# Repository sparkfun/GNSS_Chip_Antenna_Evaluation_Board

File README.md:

SparkFun GNSS Chip Antenna Evaluation Board
===========================================================

[*SparkFun GNSS Chip Antenna Eval Board (GPS-15247)*](https://www.sparkfun.com/products/15247)

The GNSS Chip Evaluation board allows for quick testing of various chip scale GPS and GNSS antennas. Various sizes and manufacturers allow the user to see for themselves how their GPS receiver will preform with each extremely small GPS antenna.

Repository Contents
-------------------

* **/Documents** - Antenna datasheets
* **/Hardware** - Eagle files

Documentation
-------------------

* **[Hookup Guide](https://learn.sparkfun.com/tutorials/gnss-chip-antenna-hookup-guide)** - Basic hookup guide for the antenna evaluation board
* **[Three Quick Tips About Using U.FL](https://learn.sparkfun.com/tutorials/three-quick-tips-about-using-ufl)** - Quick tips regarding how to connect, protect, and disconnect U.FL connectors

License Information
-------------------

This product is _**open source**_! 

Various bits of the code have different licenses applied. Anything SparkFun wrote is beerware; if you see me (or any other SparkFun employee) at the local, and you've found our code helpful, please buy us a round!

Please use, reuse, and modify these files as you see fit. Please maintain attribution to SparkFun Electronics and release anything derivative under the same license.

Distributed as-is; no warranty is given.

- Your friends at SparkFun.

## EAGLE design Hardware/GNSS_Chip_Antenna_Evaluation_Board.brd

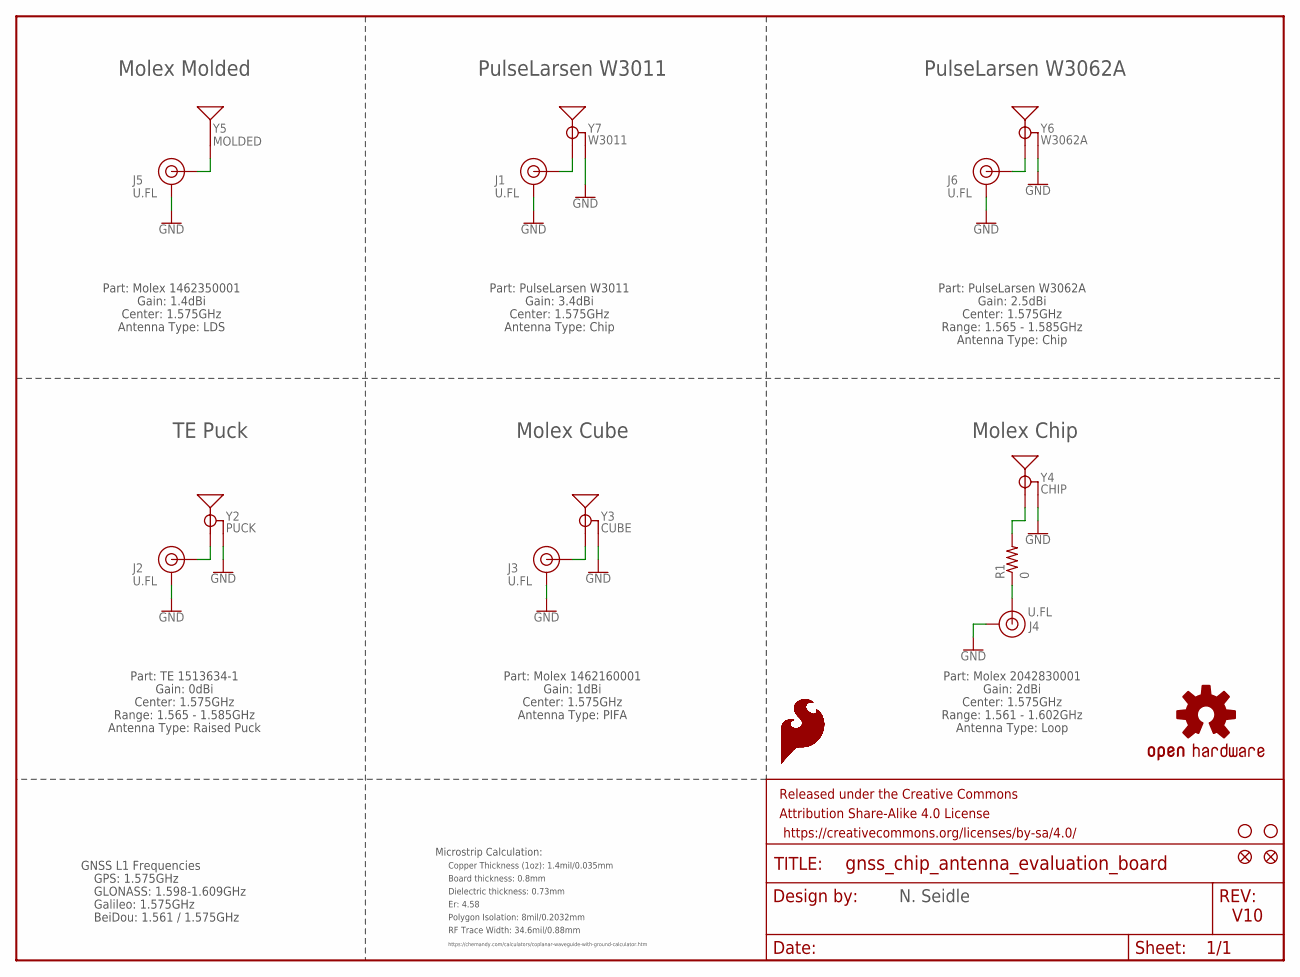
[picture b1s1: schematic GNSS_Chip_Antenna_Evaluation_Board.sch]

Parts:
FRAME1: FRAME-LETTER; CREATIVE_COMMONS
J1, J2, J3, J4, J5, J6: U.FL
JP5, JP6: STAND-OFF
JP8, JP9: FIDUCIAL1X2; FIDUCIAL-1X2
LOGO1, LOGO2, LOGO3, LOGO4, LOGO5, LOGO6: SFE_LOGO_FLAME.1EXP; SFE_LOGO_FLAME_COPPER_EXPOSED_.1
R1: 0; 0402
U$16: OSHW-LOGOS; OSHW-LOGO-S
Y2: PUCK; TE_PUCK
Y3: CUBE; MOLEX_GNSS_CUBE
Y4: CHIP; MOLEX_GNSS_CHIP
Y5: MOLDED; MLOEX_GNSS_MOLDED
Y6: W3062A
Y7: W3011

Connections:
FEED1: J1.FEED (SIGNAL), Y7.1 (SIGNAL)
FEED2: J5.FEED (SIGNAL), Y5.FEED
FEED3: J2.FEED (SIGNAL), Y2.S (SIGNAL)
FEED4: J3.FEED (SIGNAL), Y3.FEED (SIGNAL)
FEED5: J4.FEED (SIGNAL), R1.1
FEED6: J6.FEED (SIGNAL), Y6.FEED (SIGNAL)
GND: J1.1 (GND), J1.2 (GND), J2.1 (GND), J2.2 (GND), J3.1 (GND), J3.2 (GND), J4.1 (GND), J4.2 (GND), J5.1 (GND), J5.2 (GND), J6.1 (GND), J6.2 (GND), Y2.1 (GND), Y2.2 (GND), Y2.3 (GND), Y3.GND, Y4.1 (GND), Y4.2 (GND), Y4.3 (GND), Y6.GND, Y7.2 (GND), Y7.3 (GND)
unnamed: R1.2, Y4.FEED (SIGNAL)

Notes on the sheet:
V10
Board thickness: 0.8mm
Er: 4.58
Copper Thickness (1oz): 1.4mil/0.035mm
RF Trace Width: 34.6mil/0.88mm
Polygon Isolation: 8mil/0.2032mm
Dielectric thickness: 0.73mm
https://chemandy.com/calculators/coplanar-waveguide-with-ground-calculator.htm
Microstrip Calculation:
Center: 1.575GHz
Gain: 1.4dBi
Part: Molex 1462350001
Range: 1.565 - 1.585GHz
Gain: 2.5dBi
Part: PulseLarsen W3062A
Gain: 3.4dBi
Part: PulseLarsen W3011
Gain: 1dBi
Part: Molex 1462160001
Gain: 0dBi
Part: TE 1513634-1
Range: 1.561 - 1.602GHz
Gain: 2dBi
Part: Molex 2042830001
Antenna Type: Chip
Antenna Type: Loop
Antenna Type: PIFA
Antenna Type: Raised Puck
Antenna Type: LDS
GPS: 1.575GHz
GLONASS: 1.598-1.609GHz
Galileo: 1.575GHz
BeiDou: 1.561 / 1.575GHz
Molex Molded
Molex Chip
Molex Cube
PulseLarsen W3062A
PulseLarsen W3011
TE Puck
N. Seidle

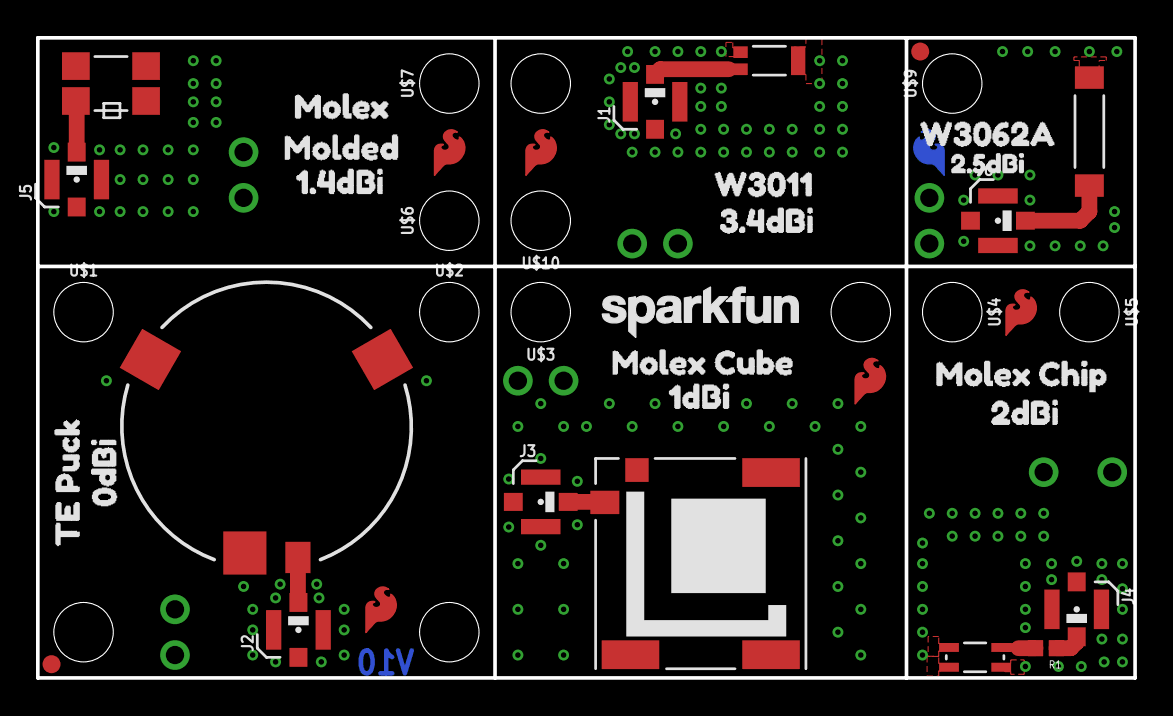
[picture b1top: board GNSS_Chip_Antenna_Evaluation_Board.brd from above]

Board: 2 copper layers, 61.0 x 35.6 mm, 74 parts (25 on the bottom side), 8 nets.

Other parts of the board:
JP1, JP2: STAND-OFF
U$1, U$2, U$3, U$4, U$5, U$6, U$7, U$9, U$10: STAND-OFF
U$8, U$24, U$25, U$26, U$27, U$28: ANCHOR0
U$11, U$34: 3#4DBI2
U$12, U$42: 0DBI0
U$13, U$57: TE_PUCK7
U$14, U$32: 1#4DBI3
U$15, U$39: 1DBI1
U$17: ORDERING_INSTRUCTIONS
U$18, U$38: 2DBI2
U$19, U$20: MOLEX_CHIP5
U$21, U$22: MOLEX0
U$23: SFE_LOGO_NAME_.1
U$29, U$30: MOLDED1
U$31, U$56: MOLEX_CUBE6
U$33, U$59: W30112
U$35, U$58: W3062A3
U$36: 2#5DBI4
U$37: SFE_LOGO_NAME_FLAME_.1
U$43: ANTENNA10
U$44: 2#5DBI2
U$50: EVALUATION_BOARD15
U$52: GNSS_CHIP13

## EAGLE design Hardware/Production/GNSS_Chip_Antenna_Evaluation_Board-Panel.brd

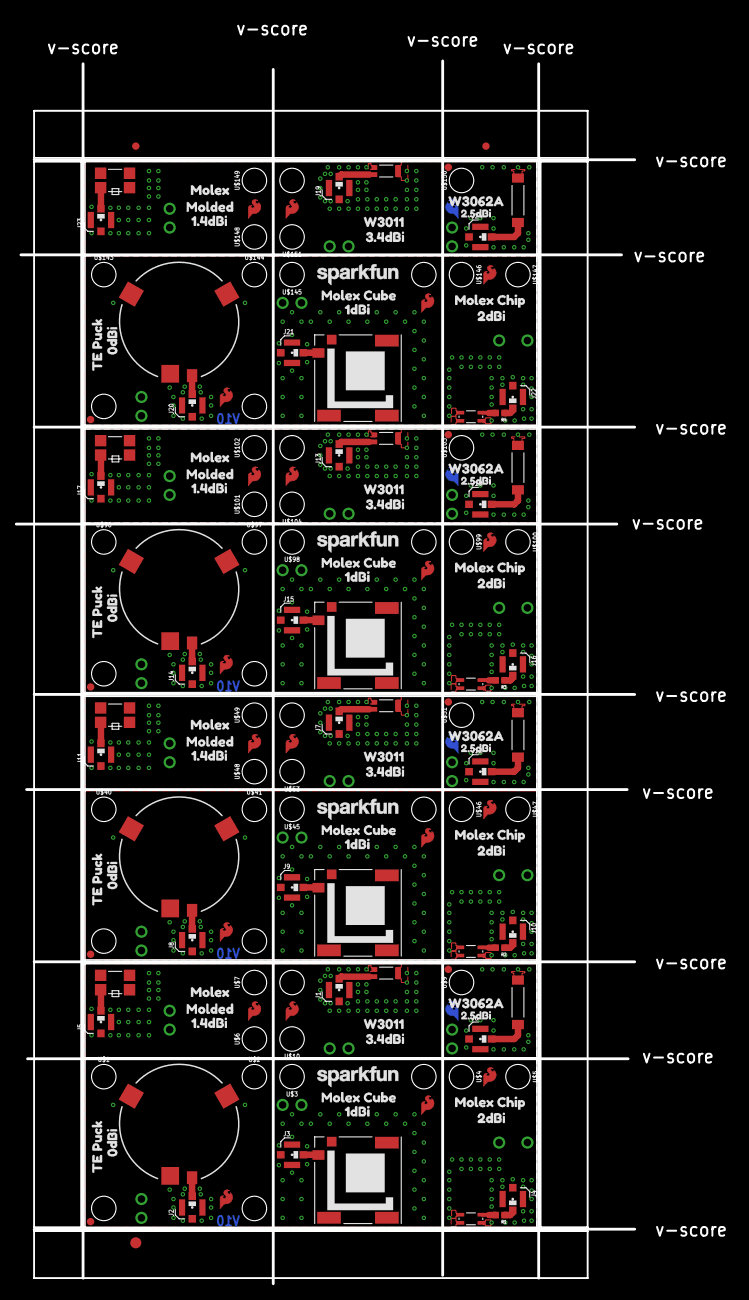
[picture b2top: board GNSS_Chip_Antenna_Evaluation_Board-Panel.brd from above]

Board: 2 copper layers, 96.6 x 171.0 mm, 291 parts (100 on the bottom side), 32 nets.

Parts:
E$1, E$2: FIDUCIAL-1X2
E$3: FIDUCIAL-1.5X3
J1, J2, J3, J4, J5, J6, J7, J8, J9, J10, J11, J12, J13, J14, J15, J16, J17, J18, J19, J20, J21, J22, J23, J24: U.FL
JP1, JP2, JP3, JP4, JP5, JP6, JP11, JP12, JP13, JP14, JP17, JP18, JP19, JP20, JP23, JP24: STAND-OFF
JP7, JP8, JP9, JP10, JP15, JP16, JP21, JP22: FIDUCIAL1X2; FIDUCIAL-1X2
LOGO1, LOGO2, LOGO3, LOGO4, LOGO5, LOGO6, LOGO7, LOGO8, LOGO9, LOGO10, LOGO11, LOGO12, LOGO13, LOGO14, LOGO15, LOGO16, LOGO17, LOGO18, LOGO19, LOGO20, LOGO21, LOGO22, LOGO23, LOGO24: SFE_LOGO_FLAME.1EXP; SFE_LOGO_FLAME_COPPER_EXPOSED_.1
R1, R2, R3, R4: 0; 0402
U$1, U$2, U$3, U$4, U$5, U$6, U$7, U$9, U$10, U$40, U$41, U$45, U$46, U$47, U$48, U$49, U$51, U$53, U$96, U$97, U$98, U$99, U$100, U$101, U$102, U$103, U$104, U$143, U$144, U$145, U$146, U$147, U$148, U$149, U$150, U$151: STAND-OFF
U$8, U$24, U$25, U$26, U$27, U$28, U$63, U$64, U$65, U$66, U$67, U$68, U$110, U$111, U$112, U$113, U$114, U$115, U$157, U$158, U$159, U$160, U$161, U$162: ANCHOR0
U$11, U$34, U$54, U$70, U$105, U$117, U$152, U$164: 3#4DBI2
U$12, U$42, U$55, U$74, U$106, U$121, U$153, U$168: 0DBI0
U$13, U$57, U$81, U$84, U$128, U$131, U$175, U$178: TE_PUCK7
U$14, U$32, U$60, U$69, U$107, U$116, U$154, U$163: 1#4DBI3
U$15, U$39, U$61, U$73, U$108, U$120, U$155, U$167: 1DBI1
U$16, U$17, U$95, U$142: OSHW-LOGOS; OSHW-LOGO-S
U$18, U$38, U$62, U$72, U$109, U$119, U$156, U$166: 2DBI2
U$19, U$20, U$85, U$86, U$132, U$133, U$179, U$180: MOLEX_CHIP5
U$21, U$22, U$87, U$89, U$134, U$136, U$181, U$183: MOLEX0
U$23, U$76, U$123, U$170: SFE_LOGO_NAME_.1
U$29, U$30, U$88, U$90, U$135, U$137, U$182, U$184: MOLDED1
U$31, U$56, U$80, U$91, U$127, U$138, U$174, U$185: MOLEX_CUBE6
U$33, U$59, U$83, U$92, U$130, U$139, U$177, U$186: W30112
U$35, U$58, U$82, U$93, U$129, U$140, U$176, U$187: W3062A3
U$36, U$71, U$118, U$165: 2#5DBI4
U$37, U$94, U$141, U$188: SFE_LOGO_NAME_FLAME_.1
U$43, U$77, U$124, U$171: ANTENNA10
U$44, U$75, U$122, U$169: 2#5DBI2
U$50, U$78, U$125, U$172: EVALUATION_BOARD15
U$52, U$79, U$126, U$173: GNSS_CHIP13
Y1, Y2, Y13, Y19: PUCK; TE_PUCK
Y3, Y8, Y14, Y20: CUBE; MOLEX_GNSS_CUBE
Y4, Y9, Y15, Y21: CHIP; MOLEX_GNSS_CHIP
Y5, Y10, Y16, Y22: MOLDED; MLOEX_GNSS_MOLDED
Y6, Y11, Y17, Y23: W3062A
Y7, Y12, Y18, Y24: W3011

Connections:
FEED1: J1.FEED, Y7.1
FEED2: J5.FEED, Y5.FEED
FEED3: J2.FEED, Y2.S
FEED4: J3.FEED, Y3.FEED
FEED5: J4.FEED, R1.1
FEED6: J6.FEED, Y6.FEED
FEED7: J7.FEED, Y12.1
FEED8: J8.FEED, Y1.S
FEED9: J9.FEED, Y8.FEED
FEED10: J10.FEED, R2.1
FEED11: J11.FEED, Y10.FEED
FEED12: J12.FEED, Y11.FEED
FEED13: J13.FEED, Y18.1
FEED14: J14.FEED, Y13.S
FEED15: J15.FEED, Y14.FEED
FEED16: J16.FEED, R3.1
FEED17: J17.FEED, Y16.FEED
FEED18: J18.FEED, Y17.FEED
FEED19: J19.FEED, Y24.1
FEED20: J20.FEED, Y19.S
FEED21: J21.FEED, Y20.FEED
FEED22: J22.FEED, R4.1
FEED23: J23.FEED, Y22.FEED
FEED24: J24.FEED, Y23.FEED
GND: J1.1, J1.2, J2.1, J2.2, J3.1, J3.2, J4.1, J4.2, J5.1, J5.2, J6.1, J6.2, Y2.1, Y2.2, Y2.3, Y3.GND, Y4.1, Y4.2, Y4.3, Y6.GND, Y7.2, Y7.3
GND1: J7.1, J7.2, J8.1, J8.2, J9.1, J9.2, J10.1, J10.2, J11.1, J11.2, J12.1, J12.2, Y1.1, Y1.2, Y1.3, Y8.GND, Y9.1, Y9.2, Y9.3, Y11.GND, Y12.2, Y12.3
GND2: J13.1, J13.2, J14.1, J14.2, J15.1, J15.2, J16.1, J16.2, J17.1, J17.2, J18.1, J18.2, Y13.1, Y13.2, Y13.3, Y14.GND, Y15.1, Y15.2, Y15.3, Y17.GND, Y18.2, Y18.3
GND3: J19.1, J19.2, J20.1, J20.2, J21.1, J21.2, J22.1, J22.2, J23.1, J23.2, J24.1, J24.2, Y19.1, Y19.2, Y19.3, Y20.GND, Y21.1, Y21.2, Y21.3, Y23.GND, Y24.2, Y24.3
unnamed: R2.2, Y9.FEED
unnamed: R1.2, Y4.FEED
unnamed: R3.2, Y15.FEED
unnamed: R4.2, Y21.FEED

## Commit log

2019-02-04 File rename
2019-02-05 Add license, readme, ignore. Add logo. Add GNSS freq table to sch. Touch up sch.
2019-02-08 Adding production panel
2019-02-21 Removing lib. Adding test result images.
2019-03-08 Pass review: Change silk. Add dims. Revise a few FPs.
2019-03-12 Add schematic title. Bump fiducials. Move version #.
2019-03-25 Corrected the polygon FP issue on the U.FL.
2019-03-25 Removing old files.

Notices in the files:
parts and their libraries:
SparkFun-Aesthetics: Licensing: CC v3.0 Share-Alike You are welcome to use this library for commercial purposes.
SparkFun-Aesthetics: Released under the Creative Commons Attribution Share-Alike 4.0 License
SparkFun-Aesthetics: https://creativecommons.org/licenses/by-sa/4.0
